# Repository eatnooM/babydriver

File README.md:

# babydriver

A small but capable force feedback board for use with GUN4IR and OpenFIRE light guns.

License: CC BY-SA 4.0

## BOM

| Reference | Part desc / number | Notes |
|----------|-------------|-------|
| Q1 | BUK98150-55A - [Mouser](https://www.mouser.com/ProductDetail/Nexperia/BUK98150-55A-CUF?qs=Yna0arPQ0CRUeN6OsRm%252BFA%3D%3D) / [LCSC](https://lcsc.com/product-detail/MOSFETs_Nexperia-BUK98150-55A-CUF_C458219.html) |  |
| D1 | RF201LAM2STR  - [Mouser](https://www.mouser.co.uk/ProductDetail/ROHM-Semiconductor/RF202LAM2STFTR?qs=HXFqYaX1Q2zHR%252BhwlkXHhw%3D%3D) / [LCSC](https://lcsc.com/product-detail/Fast-Recovery-High-Efficiency-Diodes_ROHM-Semicon-RF202LAM2STFTR_C5336592.html) | RF202LAM2S or RF302LAM2S will work fine too|
| C1 | 0.1uF - [Mouser](https://www.mouser.co.uk/ProductDetail/YAGEO/CC0603KRX7R9BB104?qs=vTakOoo5QyLvVCYM2ge8LQ%3D%3D) / [LCSC](https://www.lcsc.com/product-detail/_YAGEO-_C14663.html) |
| R1 | 1K 0603 - [Mouser](https://www.mouser.co.uk/ProductDetail/YAGEO/RC0603FR-071KL?qs=VU8sRB4EgwApHsk4rF%2F3zg%3D%3D) / [LCSC](https://lcsc.com/product-detail/Chip-Resistor-Surface-Mount_YAGEO-RC0603FR-071KL_C22548.html) | |
| R2 | 100K 0603 - [Mouser](https://www.mouser.co.uk/ProductDetail/YAGEO/RC0603FR-07100KL?qs=e1ok2LiJcmaihem8Va5%2Fsw%3D%3D) / [LCSC](https://lcsc.com/product-detail/Chip-Resistor-Surface-Mount_YAGEO-RC0603FR-07100KL_C14675.html) |  |

## Ordering

Grab the gerbers and upload to your preferred fab, or use the shared project links: [OSHPark](https://oshpark.com/shared_projects/hxcLf80E) / [PCBWay](https://www.pcbway.com/project/shareproject/babydriver_2d900780.html)

## Assembly

Considering the board is roughly the size of an SD card, the design uses 4 layers to increase thermal mass and keep the MOSFET cool during operation.
There are also no thermal reliefs due to these space constraints, so be prepared for the board to sink some heat while soldering!

Simply solder all components (watch the polarity on the diode!) and wire (looking at the side of the board with the labels):

Left side:
- G: Ground - Microcontroller ground
- S: Solenoid / rumble motor (polarity typically doesn't matter but the outer hole is positive, while the middle pad is GND when the MOSFET is active)

Right side (input):
- G: Ground - external power supply ground (can be omitted if not using an external power supply)
- D: Data pin to activate rumble / solenoid
- +: Power for force feedback
    - For solenoid, this will be the +12/+24V from your external power supply
	- For most rumble setups, this can be wired to the 3.3/5V on your microcontroller, depending on the voltage rating and power draw of the motor.

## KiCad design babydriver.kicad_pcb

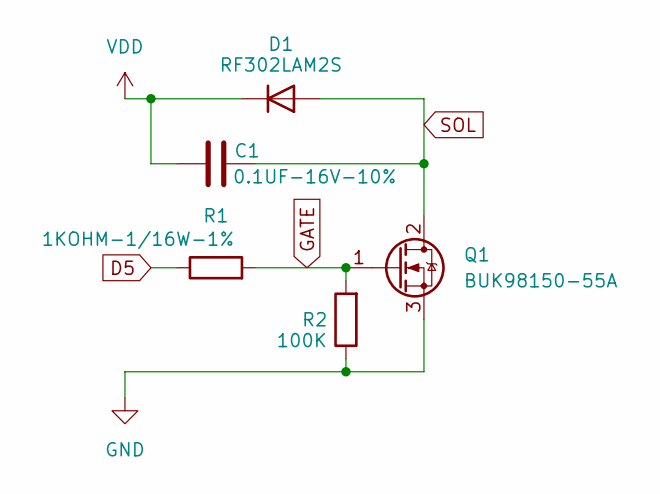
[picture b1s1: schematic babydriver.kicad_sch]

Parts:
C1: 0.1UF-16V-10%; C_0603_1608Metric_Pad1.08x0.95mm_HandSolder
D1: RF302LAM2S; D_SOD-128
Q1: BUK98150-55A; SOT-223-3_TabPin2
R1: 1KOHM-1/16W-1%; R_0603_1608Metric_Pad0.98x0.95mm_HandSolder
R2: 100K; R_0603_1608Metric_Pad0.98x0.95mm_HandSolder

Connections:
D5: R1.1
GATE: Q1.1 (G), R1.2, R2.2
GND: Q1.3 (S), R2.1
SOL: C1.1, D1.2 (A), Q1.2 (D)
VDD: C1.2, D1.1 (K)

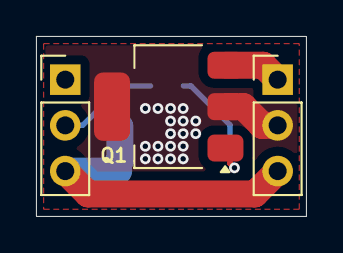
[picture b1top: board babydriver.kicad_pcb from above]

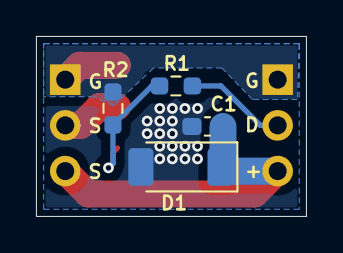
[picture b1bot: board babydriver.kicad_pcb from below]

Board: 4 copper layers, 15.0 x 10.0 mm, 5 parts (4 on the bottom side), 4 nets.

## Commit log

2025-06-22 Add project files and license
2025-06-22 Add overview to README
2025-06-22 Add pictures of both sides of board
2025-06-22 Readme cleanup
2025-06-22 Update README.md
    Add shared project links
